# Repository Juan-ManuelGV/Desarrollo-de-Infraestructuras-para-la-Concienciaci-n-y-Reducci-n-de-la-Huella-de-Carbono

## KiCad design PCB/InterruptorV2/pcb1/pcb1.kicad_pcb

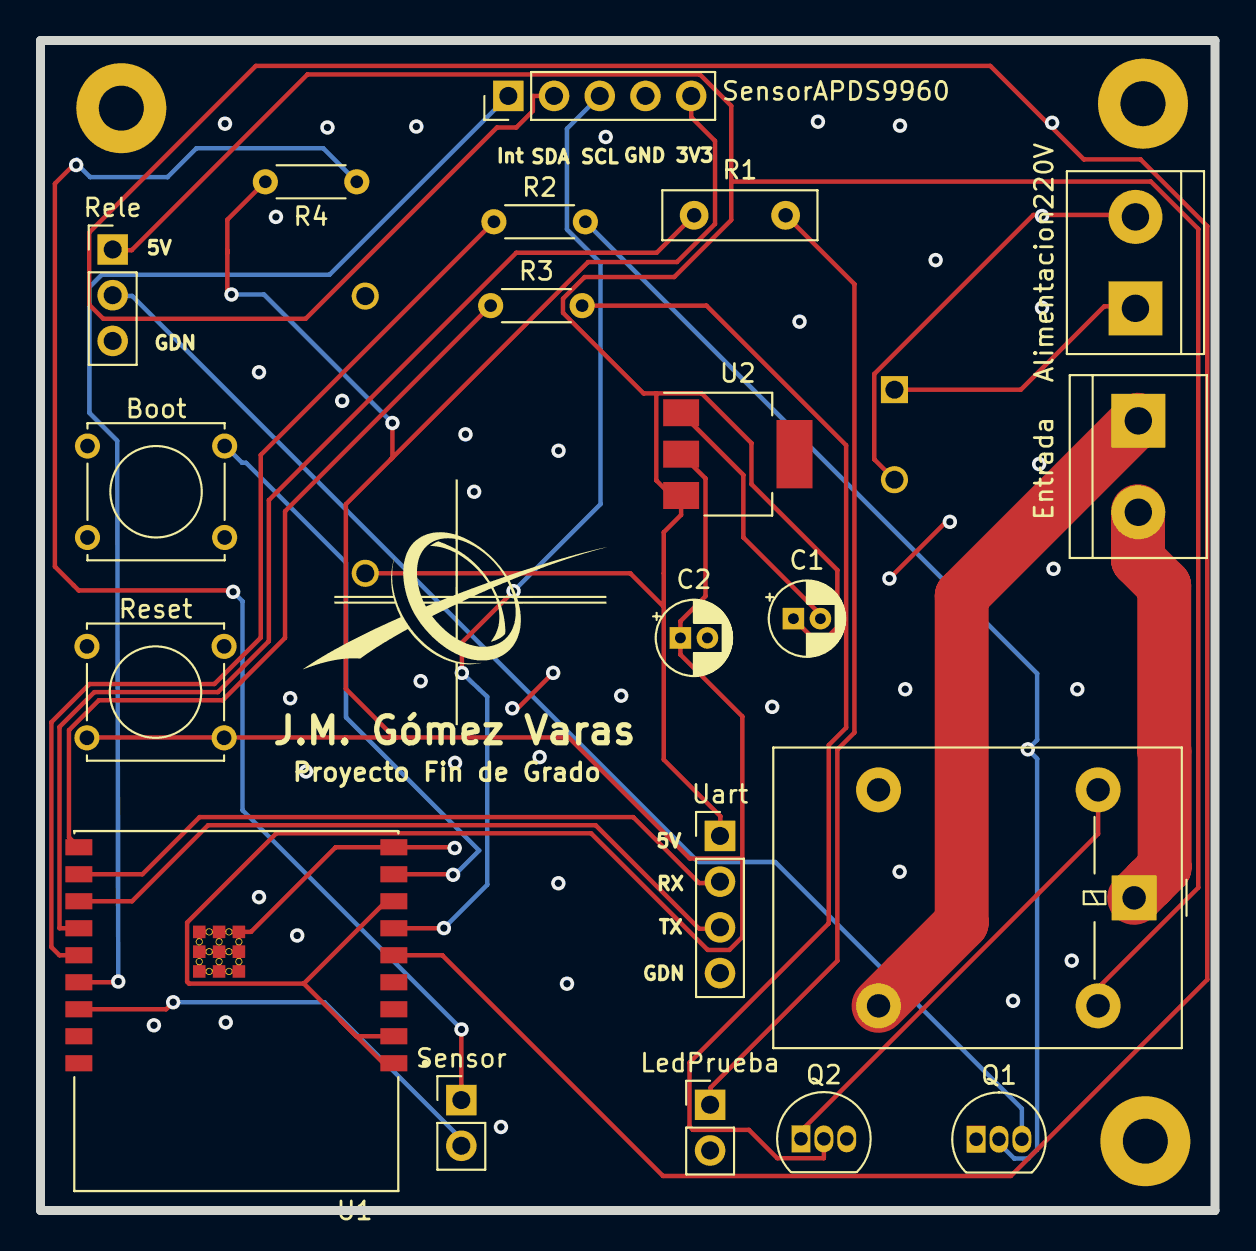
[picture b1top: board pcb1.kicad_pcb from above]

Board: 2 copper layers, 65.2 x 65.0 mm, 24 parts (1 on the bottom side), 22 nets.

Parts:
Alimentacion220V: Conn_01x02; TerminalBlock_bornier-2_P5.08mm
Boot: boton; SW_Tactile_Straight_KSL0Axx1LFTR
C1: 100uf; CP_Radial_D4.0mm_P1.50mm
C2: 10uf; CP_Radial_D4.0mm_P1.50mm
Entrada: Conn_01x02; TerminalBlock_bornier-2_P5.08mm
LedPrueba: Conn_01x02; PinHeader_1x02_P2.54mm_Vertical
PS1: HLK-PM01; CONV_HLK-PM01
Q1, Q2: NPN; TO-92_Inline
R1: R_Small_US; R_Box_L8.4mm_W2.5mm_P5.08mm
R2, R3, R4: R_Small_US; R_Axial_DIN0204_L3.6mm_D1.6mm_P5.08mm_Horizontal
REF3, REF3#2, REF3#3: MountingHole_2.5mm_Pad
Rele: Conn_01x03; PinHeader_1x03_P2.54mm_Vertical
Rele2: G5LE-1; Relay_SPDT_Omron-G5LE-1
Reset: boton; SW_Tactile_Straight_KSL0Axx1LFTR
Sensor: Conn_01x02; PinHeader_1x02_P2.54mm_Vertical
SensorAPDS9960: Conn_01x05; PinHeader_1x05_P2.54mm_Vertical
U1: ESP32-C3-WROOM-02-N4; MODULE_ESP32-C3-WROOM-02-H4
U2: AZ1117-3.3; SOT-223
Uart: Conn_01x04; PinHeader_1x04_P2.54mm_Vertical

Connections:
+3V3: C2.1, R4.2, Reset.2, SensorAPDS9960.5, U1.1 (3V3), U1.7 (IO8), U2.2 (VO)
+5V: C1.1, PS1.4 (+VO), Rele.1, Rele2.5, U2.3 (VI), Uart.1
AC: Alimentacion220V.1, PS1.1 (AC1)
E: Q1.3 (E), Rele.2
Earth: Alimentacion220V.2, PS1.2 (AC2)
GND: Boot.2, C1.2, C2.2, LedPrueba.2, PS1.3 (-VO), Q1.1 (C), Q2.3 (E), Rele.3, Reset.1, SensorAPDS9960.4, U1.9 (GND), U1.19 (GND), U1.20 (GND), U1.21 (GND), U1.22 (GND), U1.23 (GND), U1.24 (GND), U1.25 (GND), U1.26 (GND), U1.27 (GND), U1.28 (GND), U1.29 (GND), U1.30 (GND), U1.31 (GND), U1.32 (GND), U1.33 (GND), U1.34 (GND), U1.35 (GND), U1.36 (GND), U1.37 (GND), U1.38 (GND), U1.39 (GND), U2.1 (GND), Uart.4
INT: SensorAPDS9960.1, U1.15 (IO3)
LP: R1.1, U1.13 (IO18)
unnamed: Entrada.1, Rele2.4
unnamed: Entrada.2, Rele2.1
unnamed: LedPrueba.1, R1.2
unnamed: Q1.2 (B), R2.2
unnamed: Q2.2 (B), R3.2
unnamed: Q2.1 (C), Rele2.2
unnamed: R4.1, Sensor.1
unnamed: U1.11 (RXD), Uart.2
unnamed: U1.12 (TXD), Uart.3
ReD: R2.1, U1.14 (IO19)
SCL: SensorAPDS9960.3, U1.6 (IO7)
SDA: SensorAPDS9960.2, U1.5 (IO6)
rele: R3.1, U1.10 (IO10)
sen: Sensor.2, U1.16 (IO2)

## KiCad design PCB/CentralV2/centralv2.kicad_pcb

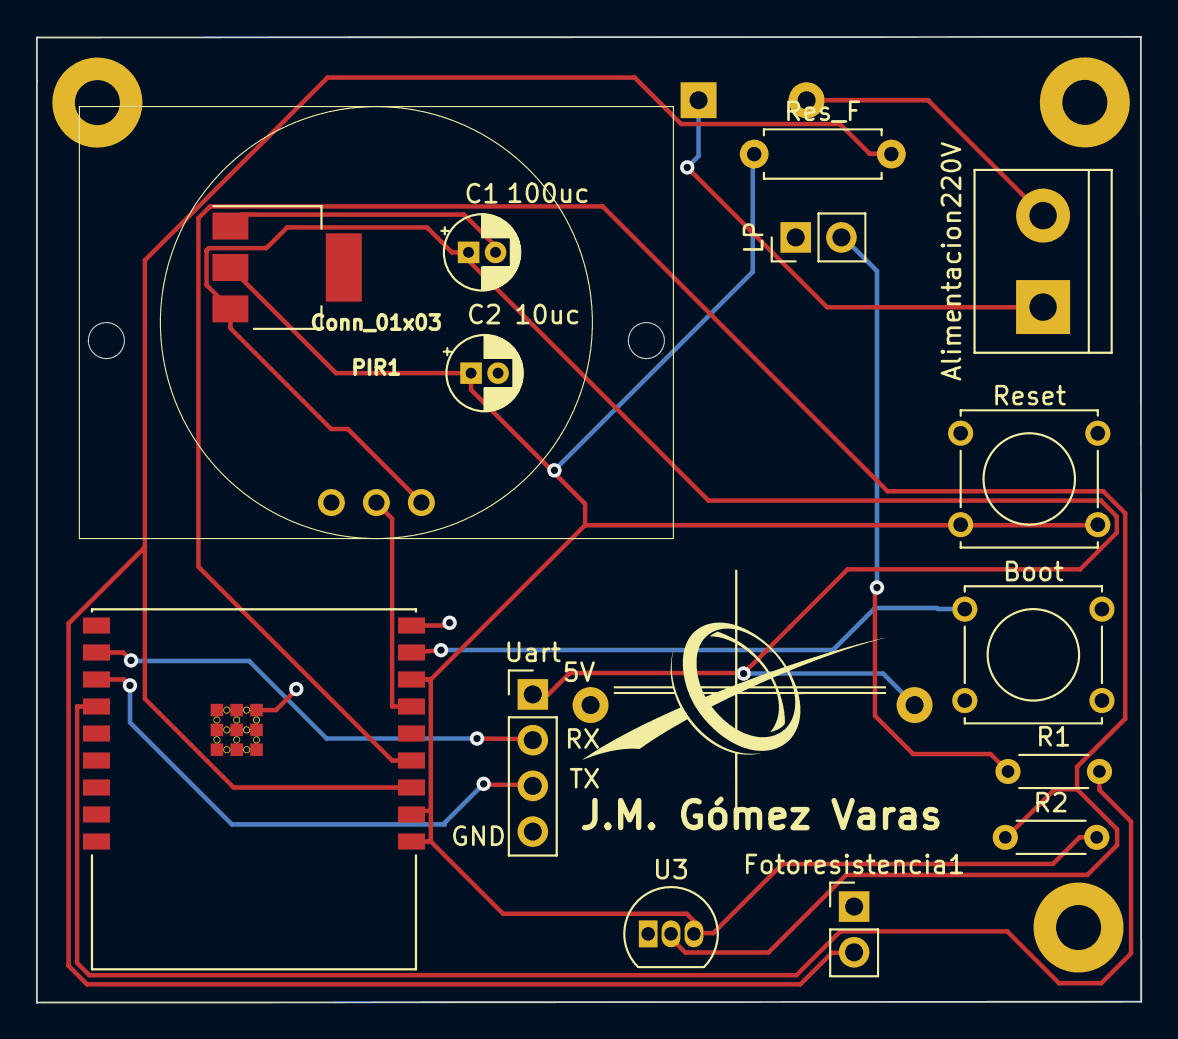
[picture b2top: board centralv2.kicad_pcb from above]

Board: 2 copper layers, 61.4 x 53.6 mm, 19 parts (1 on the bottom side), 12 nets.

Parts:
Alimentacion220V: Conn_01x02; TerminalBlock_bornier-2_P5.08mm
Boot: boton; SW_Tactile_Straight_KSL0Axx1LFTR
C1: 100uf; CP_Radial_D4.0mm_P1.50mm
C2: 10uf; CP_Radial_D4.0mm_P1.50mm
Fotoresistencia1: PinHeader_1x02_P2.54mm_Vertical
LP: Conn_01x02; PinHeader_1x02_P2.54mm_Vertical
PIR1: Conn_01x03; HC-SR501
PS2: HLK-5M05; Converter_ACDC_HiLink_HLK-5Mxx
R1, R2: R_Small_US; R_Axial_DIN0204_L3.6mm_D1.6mm_P5.08mm_Horizontal
REF3, REF3#2, REF3#3: MountingHole_2.5mm_Pad
Res_F: R_Axial_DIN0207_L6.3mm_D2.5mm_P7.62mm_Horizontal
Reset: boton; SW_Tactile_Straight_KSL0Axx1LFTR
U1: ESP32-C3-WROOM-02-N4; MODULE_ESP32-C3-WROOM-02-H4
U2: AZ1117-3.3; SOT-223
U3: DS18B20; TO-92_Inline
Uart: Conn_01x04; PinHeader_1x04_P2.54mm_Vertical

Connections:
+3V3: C2.1, R2.2, Reset.2, U1.1 (3V3), U1.7 (IO8), U2.2 (VO), U3.3 (V_{DD})
+5V: C1.1, PIR1.3, PS2.4 (+Vout), U2.3 (VI), Uart.1
AC: Alimentacion220V.1, PS2.1 (AC/L)
Earth: Alimentacion220V.2, PS2.2 (AC/N)
Fresistor: Fotoresistencia1.2, Res_F.2, U1.3 (IO4)
GND: Boot.2, C1.2, C2.2, Fotoresistencia1.1, LP.1, PIR1.1, PS2.3 (-Vout), Reset.1, U1.9 (GND), U1.19 (GND), U1.20 (GND), U1.21 (GND), U1.22 (GND), U1.23 (GND), U1.24 (GND), U1.25 (GND), U1.26 (GND), U1.27 (GND), U1.28 (GND), U1.29 (GND), U1.30 (GND), U1.31 (GND), U1.32 (GND), U1.33 (GND), U1.34 (GND), U1.35 (GND), U1.36 (GND), U1.37 (GND), U1.38 (GND), U1.39 (GND), U2.1 (GND), U3.1 (GND), Uart.4
Led: R1.2, U1.13 (IO18)
unnamed: LP.2, R1.1
unnamed: U1.11 (RXD), Uart.2
unnamed: U1.12 (TXD), Uart.3
PIR: PIR1.2, U1.6 (IO7)
tem: R2.1, U1.4 (IO5), U3.2 (DQ)

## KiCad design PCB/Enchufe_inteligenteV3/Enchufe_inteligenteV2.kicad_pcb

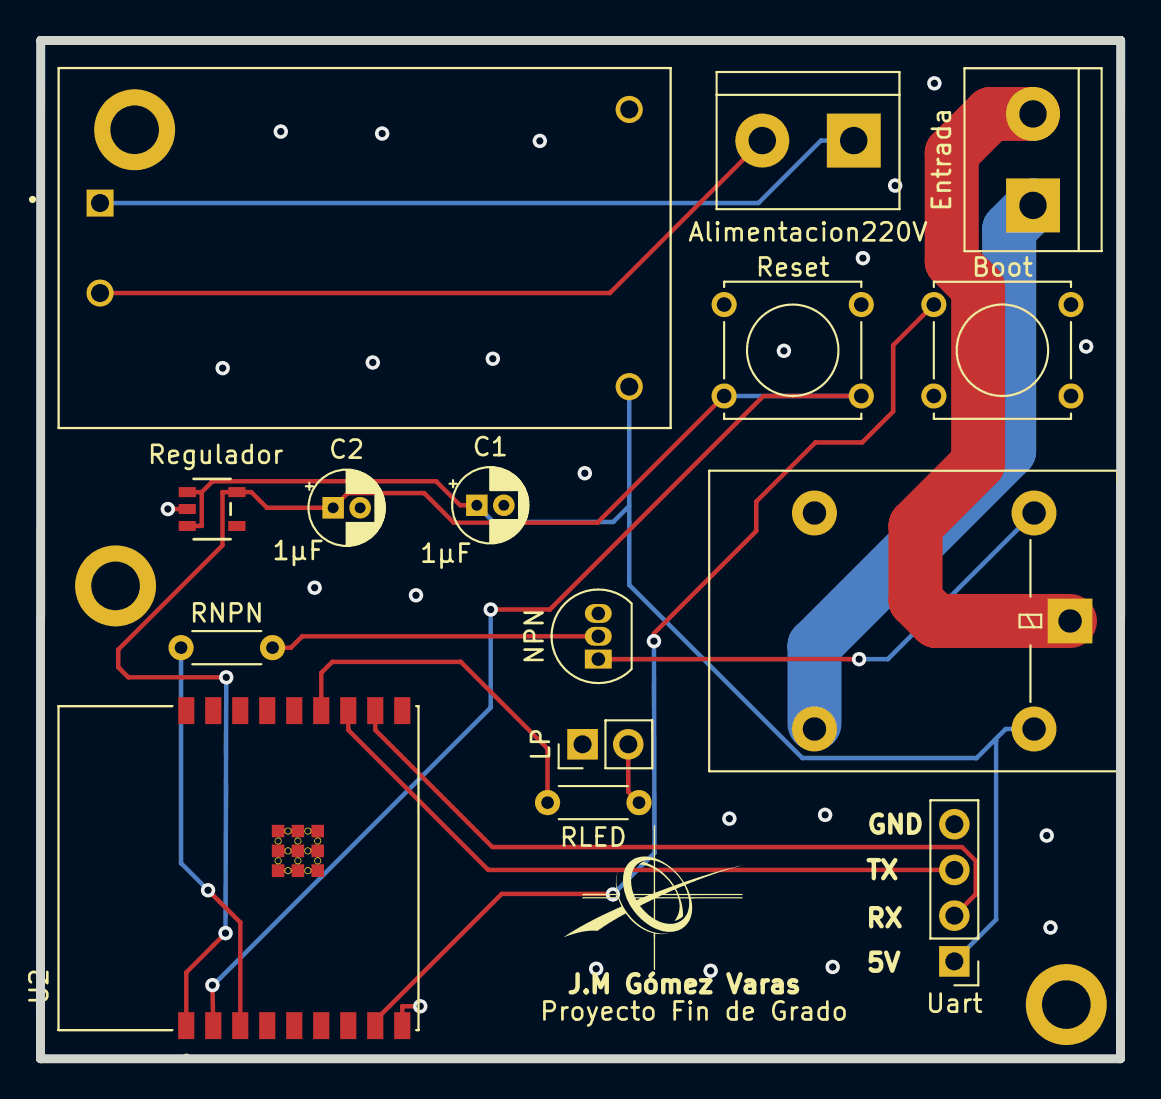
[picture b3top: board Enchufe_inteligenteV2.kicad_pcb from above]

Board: 2 copper layers, 60.0 x 56.6 mm, 17 parts (0 on the bottom side), 15 nets.

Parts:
Alimentacion220V: Conn_01x02; TerminalBlock_bornier-2_P5.08mm
Boot: boton; SW_Tactile_Straight_KSL0Axx1LFTR
C1, C2: 1µF; CP_Radial_D4.0mm_P1.50mm
Entrada: Conn_01x02; TerminalBlock_bornier-2_P5.08mm
LP: Conn_01x02; PinHeader_1x02_P2.54mm_Vertical
NPN: NPN; TO-92_Inline
PS1: HLK-PM0; CONV_HLK-PM01
REF1, REF2: MountingHole_2.7mm_M2.5_ISO14580_Pad
RLED: R_Small_US; R_Axial_DIN0204_L3.6mm_D1.6mm_P5.08mm_Horizontal
RNPN: R_Small_US; R_Axial_DIN0204_L3.6mm_D1.6mm_P5.08mm_Horizontal
Regulador: RT9080-33GJ5
Rele: G5LE-1; Relay_SPDT_Omron-G5LE-1
Reset: boton; SW_Tactile_Straight_KSL0Axx1LFTR
U2: ESP32-C3-WROOM-02-N4; MODULE_ESP32-C3-WROOM-02-H4
Uart: Conn_01x04; PinHeader_1x04_P2.54mm_Vertical

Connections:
+3V3: C2.1, Regulador.5 (VOUT), Reset.2, U2.1 (3V3)
+5V: C1.1, PS1.4 (+VO), Regulador.1 (VIN), Regulador.3 (EN), Rele.5, Uart.1
AC: Alimentacion220V.1, PS1.1 (AC1)
Earth: Alimentacion220V.2, PS1.2 (AC2)
GND: Boot.2, C1.2, C2.2, LP.1, NPN.3 (E), PS1.3 (-VO), Regulador.2 (GND), Reset.1, U2.9 (GND), U2.19 (GND), U2.20 (GND), U2.21 (GND), U2.22 (GND), U2.23 (GND), U2.24 (GND), U2.25 (GND), U2.26 (GND), U2.27 (GND), U2.28 (GND), U2.29 (GND), U2.30 (GND), U2.31 (GND), U2.32 (GND), U2.33 (GND), U2.34 (GND), U2.35 (GND), U2.36 (GND), U2.37 (GND), U2.38 (GND), U2.39 (GND), Uart.4
Led: RLED.2, U2.13 (IO18)
unnamed: Entrada.1, Rele.4
unnamed: Entrada.2, Rele.1
unnamed: LP.2, RLED.1
unnamed: NPN.2 (B), RNPN.2
unnamed: NPN.1 (C), Rele.2
unnamed: U2.11 (RXD), Uart.2
unnamed: U2.12 (TXD), Uart.3
boot: Boot.1, U2.8 (IO9)
rele: RNPN.1, U2.3 (IO4)

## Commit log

2026-02-10 PFG_v1

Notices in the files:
parts and their libraries:
Copyright 2016 Accelerated Designs. All rights reserved.
